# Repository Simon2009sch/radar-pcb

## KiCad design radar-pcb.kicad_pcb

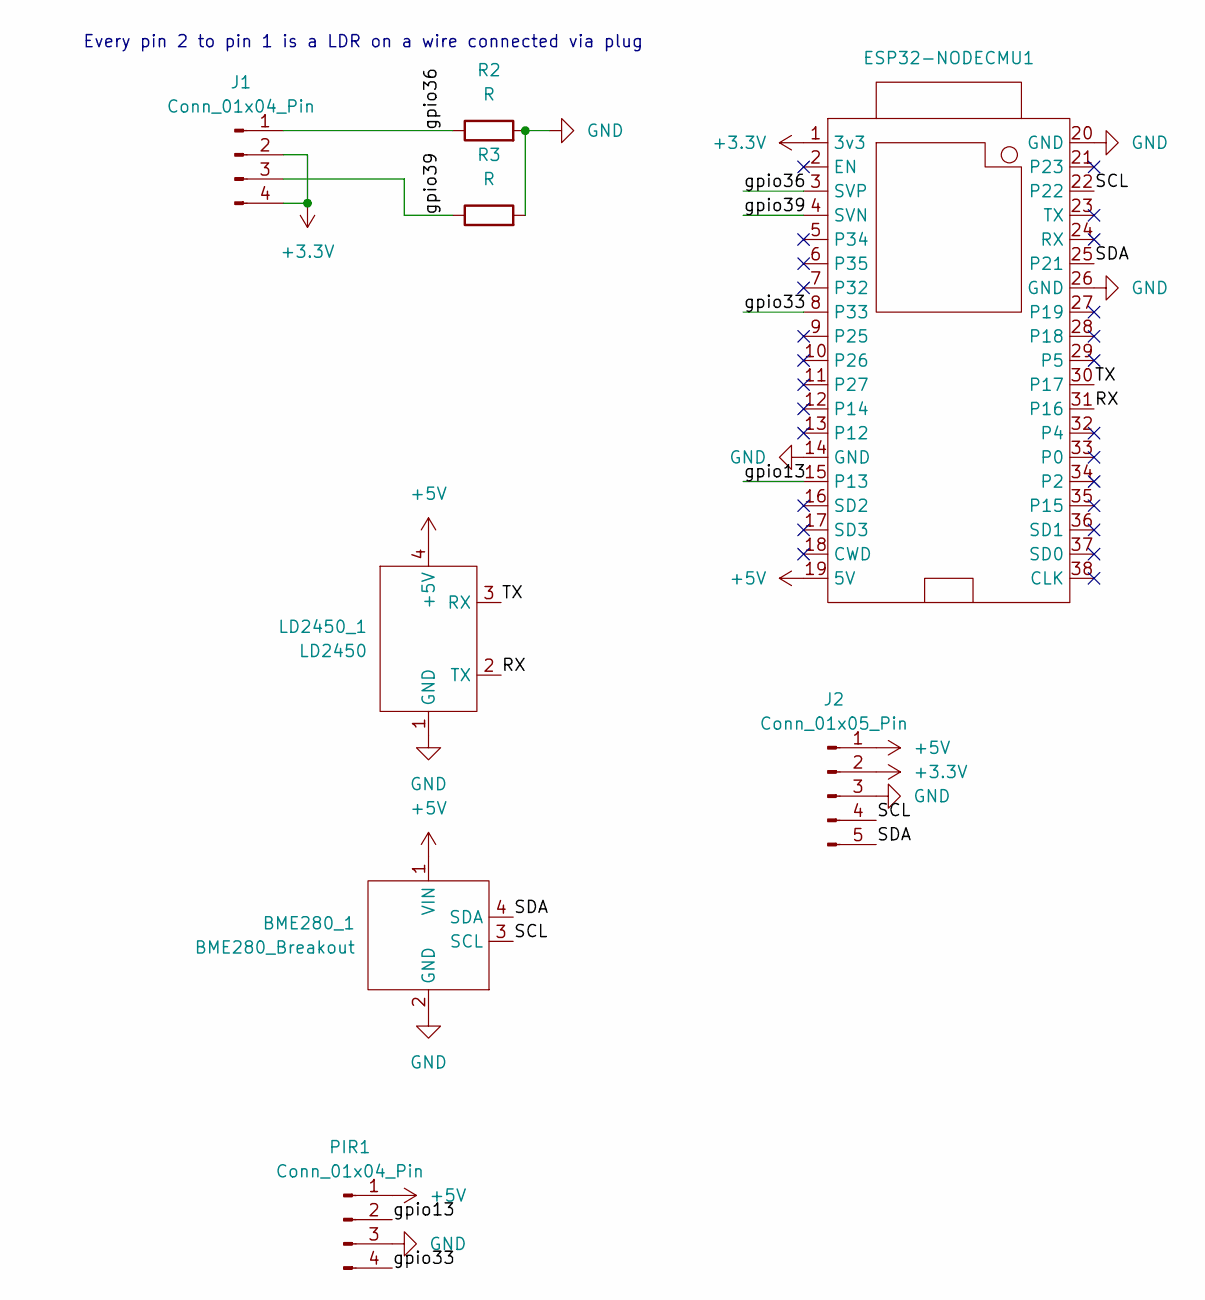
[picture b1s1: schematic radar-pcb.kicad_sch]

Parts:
BME280_1: BME280_Breakout; JST_XH_B4B-XH-A_1x04_P2.50mm_Vertical
ESP32-NODECMU1: ESP32S-NODEMCU-Pin-Socket
J1: Conn_01x04_Pin; JST_XH_B4B-XH-A_1x04_P2.50mm_Vertical
J2: Conn_01x05_Pin; PinSocket_1x05_P2.54mm_Vertical
LD2450_1: LD2450; JST_XH_B4B-XH-A_1x04_P2.50mm_Vertical
PIR1: Conn_01x04_Pin; JST_XH_B4B-XH-A_1x04_P2.50mm_Vertical
R2, R3: R; R_Axial_DIN0207_L6.3mm_D2.5mm_P10.16mm_Horizontal

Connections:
+3.3V: ESP32-NODECMU1.1 (3v3), J1.2, J1.4, J2.2
+5V: BME280_1.1 (VIN), ESP32-NODECMU1.19 (5V), J2.1, LD2450_1.4 (+5V), PIR1.1
/RX: ESP32-NODECMU1.31 (P16), LD2450_1.2 (TX)
/SCL: BME280_1.3 (SCL), ESP32-NODECMU1.22, J2.4
/SDA: BME280_1.4 (SDA), ESP32-NODECMU1.25 (P21), J2.5
/TX: ESP32-NODECMU1.30 (P17), LD2450_1.3 (RX)
/gpio13: ESP32-NODECMU1.15 (P13), PIR1.2
/gpio33: ESP32-NODECMU1.8 (P33), PIR1.4
/gpio36: ESP32-NODECMU1.3 (SVP), J1.1, R2.1
/gpio39: ESP32-NODECMU1.4 (SVN), J1.3, R3.1
GND: BME280_1.2 (GND), ESP32-NODECMU1.14 (GND), ESP32-NODECMU1.20 (GND), ESP32-NODECMU1.26 (GND), J2.3, LD2450_1.1 (GND), PIR1.3, R2.2, R3.2

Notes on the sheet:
Every pin 2 to pin 1 is a LDR on a wire connected via plug

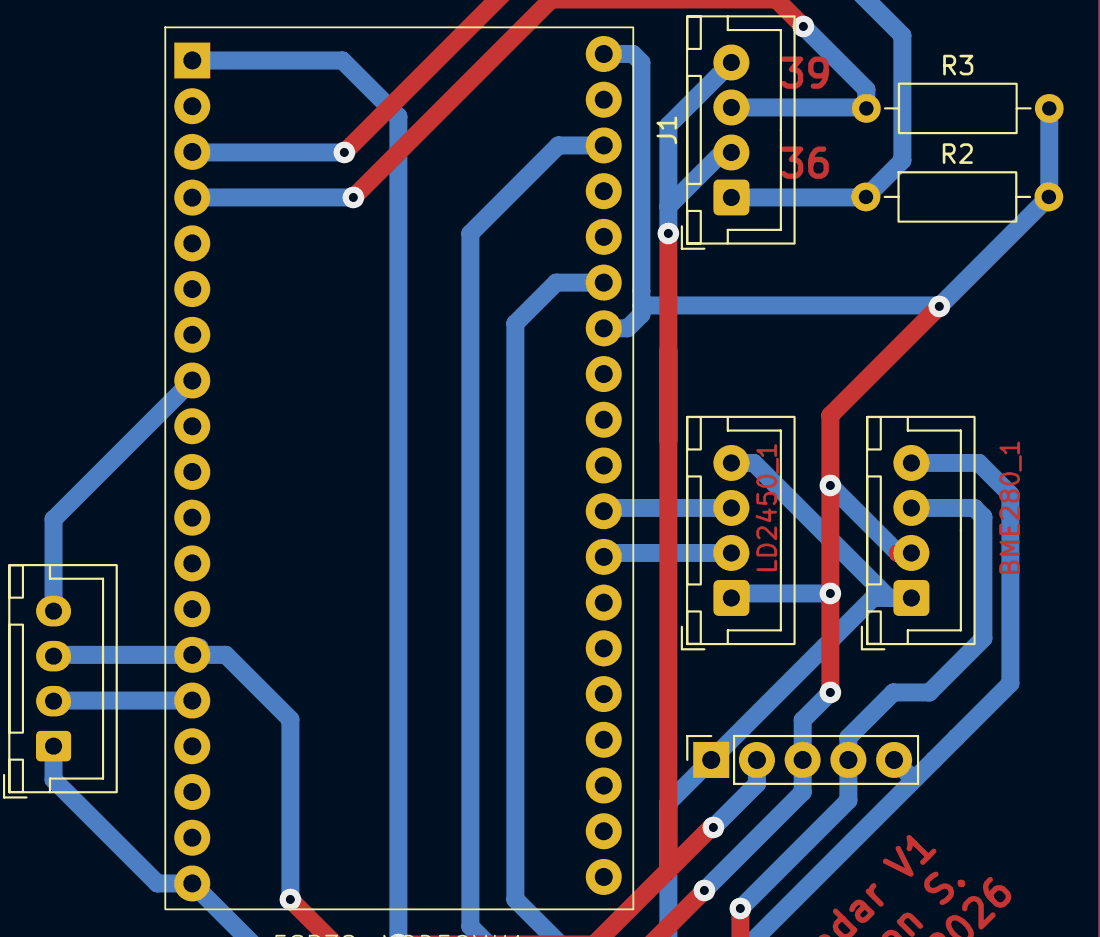
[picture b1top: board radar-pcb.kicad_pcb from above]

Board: 2 copper layers, 8 parts (0 on the bottom side), 11 nets.
